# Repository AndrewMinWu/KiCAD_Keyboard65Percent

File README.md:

# Custom 65% Keyboard PCB

## Repository Structure

```text
├── Hardware/          # Schematic, PCB, and gerber files
├── Firmware/          # Firmware files
└── Libraries_And_Datasheets/              # Datasheets and libraries (from ai03) for keyboard parts. 
```

## Purpose & Motivation

When I was 15, I bought my first custom mechanical keyboard: a QK60 from Qwertykeys alongside Gateron yellow switches and some cheap keycaps from amazon. However, I encountered a problem when I accidently took out the PCB with the JST connector still plugged in, ripping the socket on the daughterboard (where the usb-c was). Devastated, this experience essentially brought me into PCB design through online guides and communities. 2 years later, with more PCB design experience, I decided to create my own 65% keyboard (my personal favorite form factor. Who uses the numpad anyways!?).     

## Design

### Component List (BOM)
1. ATmega32U4 8-bit AVR Microcontroller ([Datasheet](http://ww1.microchip.com/downloads/en/DeviceDoc/Atmel-7766-8-bit-AVR-ATmega16U4-32U4_Datasheet.pdf))
2. ECS-160 16.000MHz SMD Crystal 3225 4-Pin ([Datasheet](https://ecsxtal.com/store/pdf/ECX-32.pdf))
3. GCT USB4105-GF-A USB-C Receptacle 16P SMD RA ([Datasheet](https://gct.co/files/drawings/usb4105.pdf))
4. Keyboard Switches (MX, taken from ai03's library)
5. 1N4148 / 1N4148W Switching Diodes
6. Passives & Miscellaneous Hardware:
   - Capacitors (0805, Ceramic)
   - Resistors (0805)
   - Tactile Push Button (Reset Switch)

### PCB, Schematic, 3D Render

The full PCB was designed with KiCAD

## Firmware

The firmware for this keyboard is built using QMK. While the framework is C-based, configuring the board primarily involved utilizing the standard QMK file structure to define the hardware and layout:
* **`info.json` & `config.h`:** Keyboard matrix, MCU definitions, and hardware config
* **`rules.mk`:** Bootloader selection
* **`keymap.c`:** Keymap and layer definitions (able to change config with VIA)

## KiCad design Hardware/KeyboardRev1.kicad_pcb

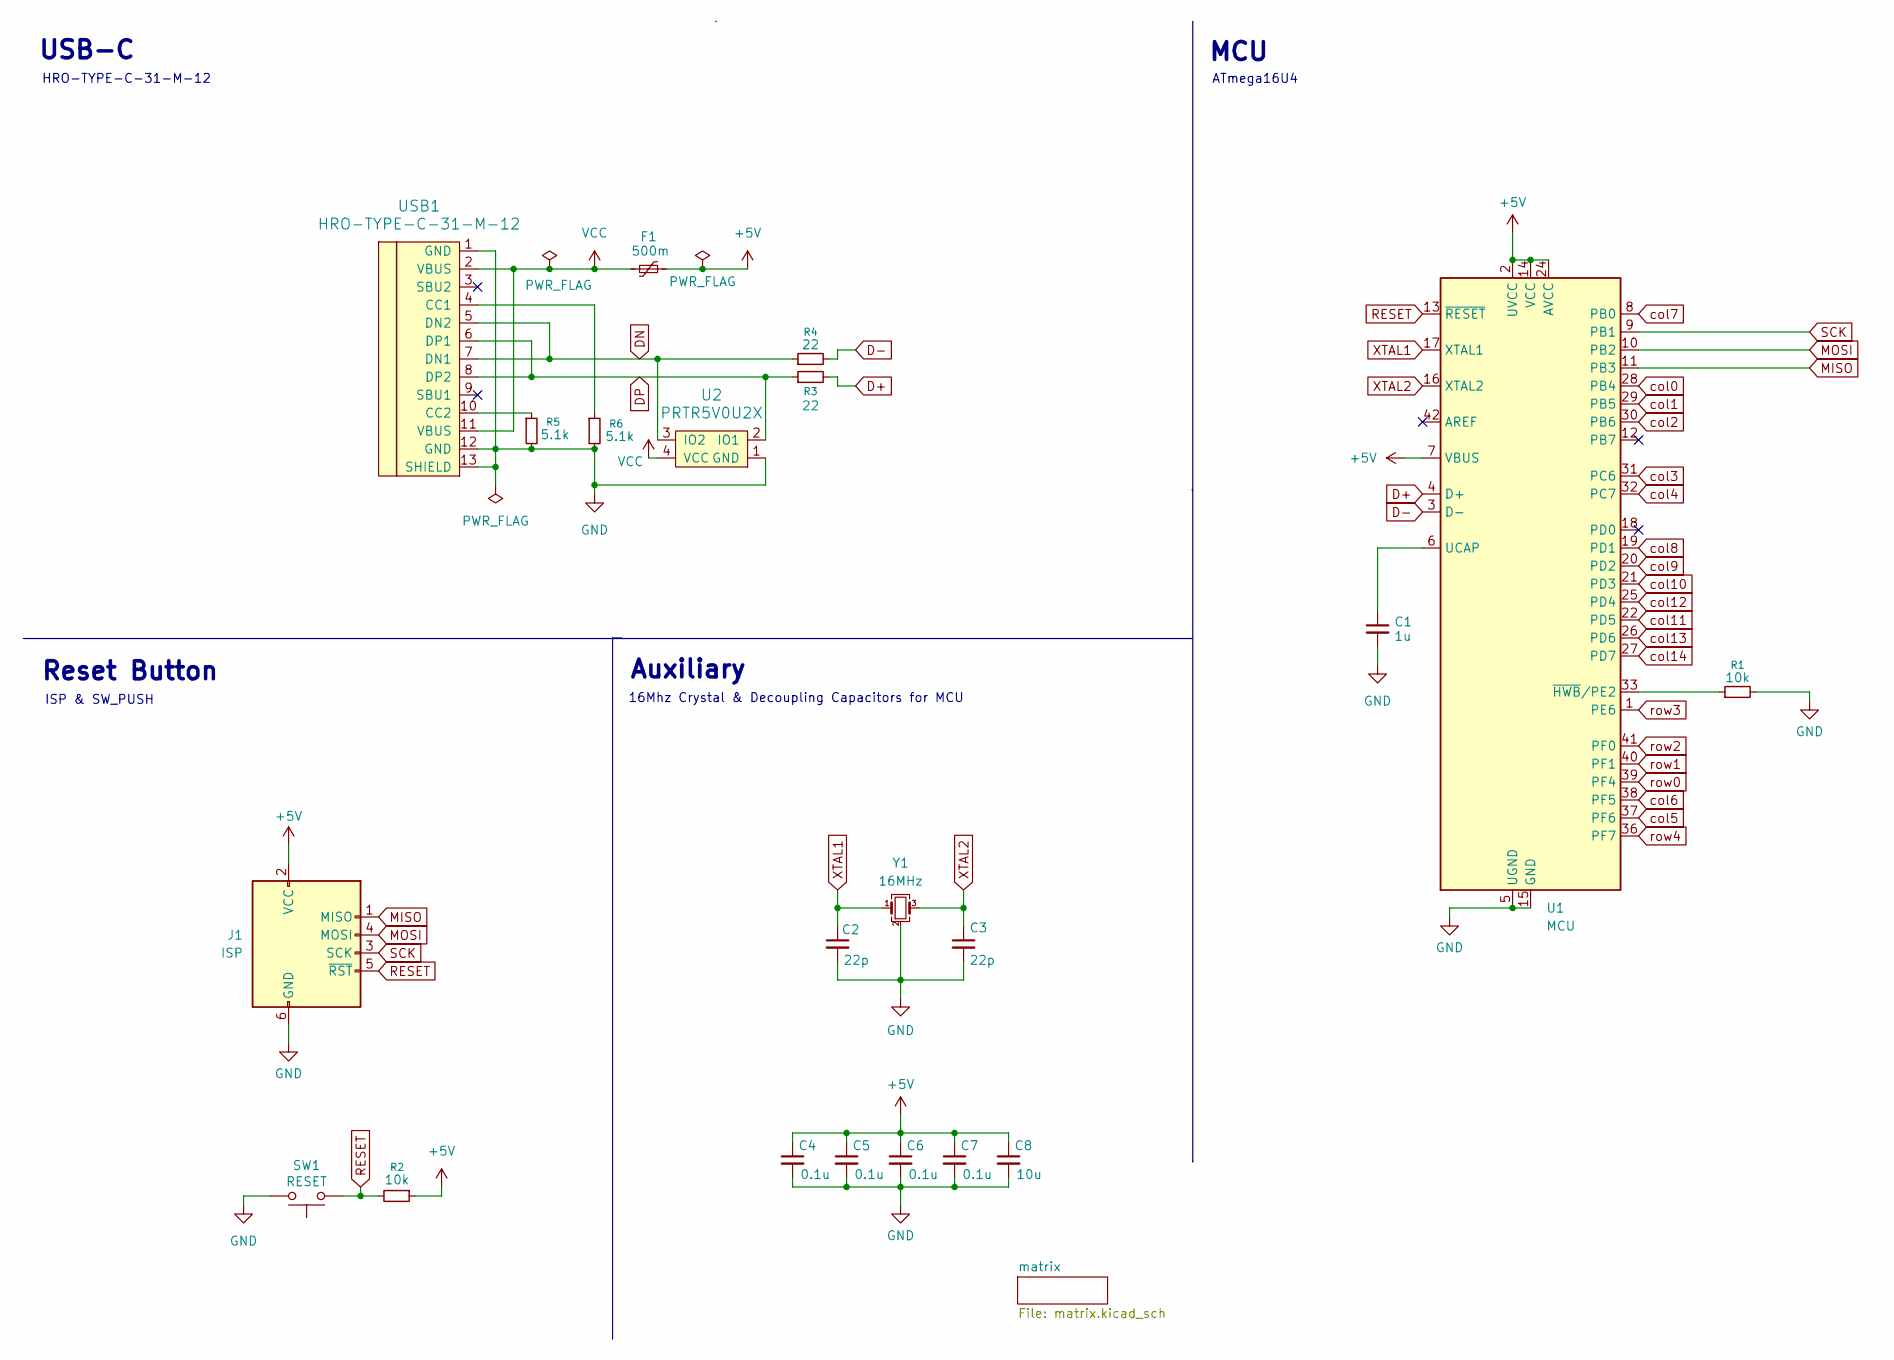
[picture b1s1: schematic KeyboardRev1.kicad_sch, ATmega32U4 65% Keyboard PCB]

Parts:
C1: 1u; C_0805_2012Metric_Pad1.18x1.45mm_HandSolder
C2, C3: 22p; C_0805_2012Metric_Pad1.18x1.45mm_HandSolder
C4, C5, C6, C7: 0.1u; C_0805_2012Metric_Pad1.18x1.45mm_HandSolder
C8: 10u; C_0805_2012Metric_Pad1.18x1.45mm_HandSolder
F1: 500m; Fuse_1206_3216Metric_Pad1.42x1.75mm_HandSolder
J1: ISP; Reset_Pretty-Mask
R1, R2: 10k; R_0805_2012Metric_Pad1.20x1.40mm_HandSolder
R3, R4: 22; R_0805_2012Metric_Pad1.20x1.40mm_HandSolder
R5, R6: 5.1k; R_0805_2012Metric_Pad1.20x1.40mm_HandSolder
SW1: RESET; SW_SPST_SKQG_WithStem
U1: MCU; TQFP-44_10x10mm_P0.8mm
U2: PRTR5V0U2X; SOT143B
USB1: HRO-TYPE-C-31-M-12; HRO-TYPE-C-31-M-12-HandSoldering
Y1: 16MHz; Crystal_SMD_3225-4Pin_3.2x2.5mm_HandSoldering

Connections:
+5V: C4.1, C5.1, C6.1, C7.1, C8.1, F1.2, J1.2 (VCC), R2.1, U1.2 (UVCC), U1.7 (VBUS), U1.14 (VCC), U1.24 (AVCC), U1.34 (VCC), U1.44 (AVCC)
D+: R3.2, U1.4 (D+)
D-: R4.2, U1.3 (D-)
DN: R4.1, U2.3 (IO2), USB1.5 (DN2), USB1.7 (DN1)
DP: R3.1, U2.2 (IO1), USB1.6 (DP1), USB1.8 (DP2)
GND: C1.2, C2.2, C3.2, C4.2, C5.2, C6.2, C7.2, C8.2, J1.6 (GND), R1.2, R5.2, R6.2, SW1.2, U1.5 (UGND), U1.15 (GND), U1.23 (GND), U1.35 (GND), U1.43 (GND), U2.1 (GND), USB1.1 (GND), USB1.12 (GND), USB1.13 (SHIELD), Y1.2 (G), Y1.4 (G)
MISO: J1.1 (MISO), U1.11 (PB3)
MOSI: J1.4 (MOSI), U1.10 (PB2)
unnamed: C1.1, U1.6 (UCAP)
unnamed: R1.1, U1.33 (~HWB/PE2)
unnamed: R6.1, USB1.4 (CC1)
unnamed: R5.1, USB1.10 (CC2)
RESET: J1.5 (~RST), R2.2, SW1.1, U1.13 (~RESET)
SCK: J1.3 (SCK), U1.9 (PB1)
VCC: F1.1, U2.4 (VCC), USB1.2 (VBUS), USB1.11 (VBUS)
XTAL1: C2.1, U1.17 (XTAL1), Y1.1
XTAL2: C3.1, U1.16 (XTAL2), Y1.3
col0: U1.28 (PB4); also elsewhere on the board
col1: U1.29 (PB5); also elsewhere on the board
col2: U1.30 (PB6); also elsewhere on the board
col3: U1.31 (PC6); also elsewhere on the board
col4: U1.32 (PC7); also elsewhere on the board
col5: U1.37 (PF6); also elsewhere on the board
col6: U1.38 (PF5); also elsewhere on the board
col7: U1.8 (PB0); also elsewhere on the board
col8: U1.19 (PD1); also elsewhere on the board
col9: U1.20 (PD2); also elsewhere on the board
col10: U1.21 (PD3); also elsewhere on the board
col11: U1.22 (PD5); also elsewhere on the board
col12: U1.25 (PD4); also elsewhere on the board
col13: U1.26 (PD6); also elsewhere on the board
col14: U1.27 (PD7); also elsewhere on the board
row0: U1.39 (PF4); also elsewhere on the board
row1: U1.40 (PF1); also elsewhere on the board
row2: U1.41 (PF0); also elsewhere on the board
row3: U1.1 (PE6); also elsewhere on the board
row4: U1.36 (PF7); also elsewhere on the board

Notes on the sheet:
16Mhz Crystal & Decoupling Capacitors for MCU
ATmega16U4
ISP & SW_PUSH
HRO-TYPE-C-31-M-12
Reset Button
USB-C
MCU
Auxiliary

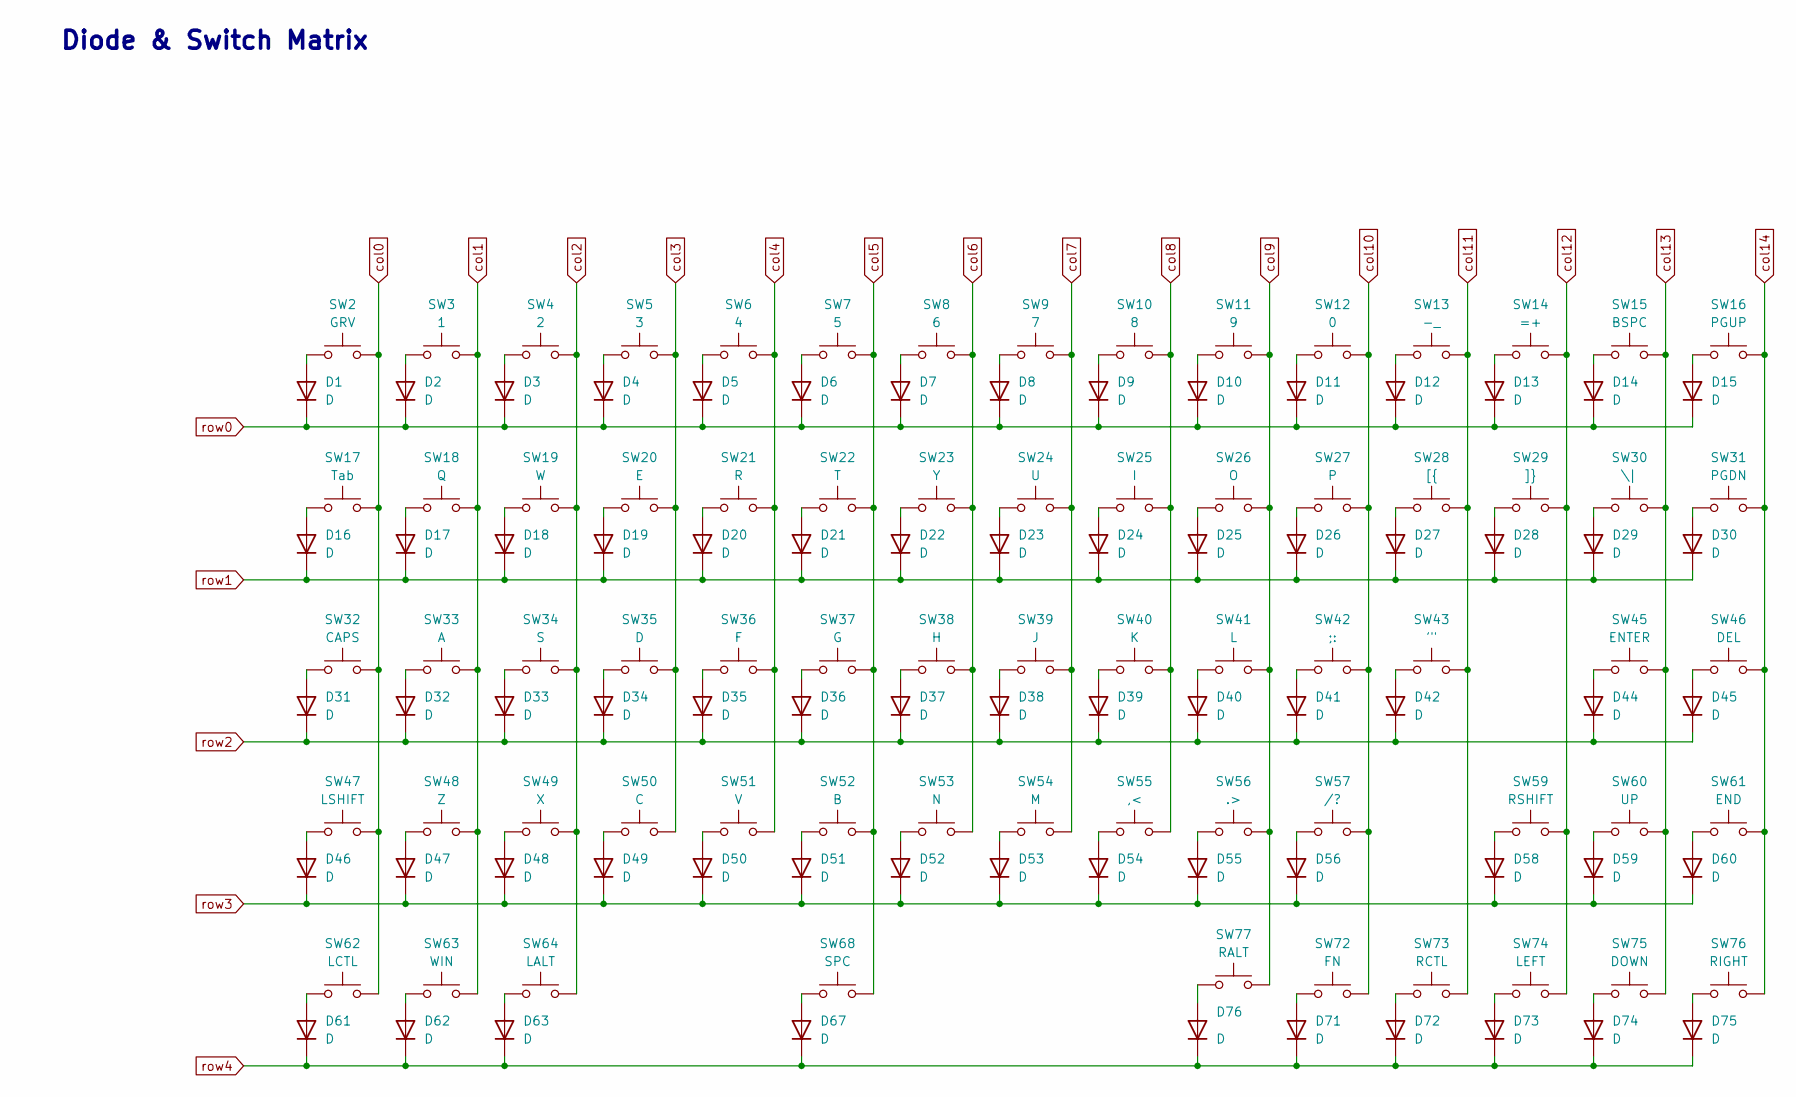
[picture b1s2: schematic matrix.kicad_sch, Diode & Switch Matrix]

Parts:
D1, D2, D3, D4, D5, D6, D7, D8, D9, D10, D11, D12, D13, D14, D15, D16, D17, D18, D19, D20, D21, D22, D23, D24, D25, D26, D27, D28, D29, D30, D31, D32, D33, D34, D35, D36, D37, D38, D39, D40, D41, D42, D44, D45, D46, D47, D48, D49, D50, D51, D52, D53, D54, D55, D56, D58, D59, D60, D61, D62, D63, D67, D71, D72, D73, D74, D75, D76: D; D_SOD-123
SW2: GRV; SW_Cherry_MX_1.00u_PCB
SW3: 1; SW_Cherry_MX_1.00u_PCB
SW4: 2; SW_Cherry_MX_1.00u_PCB
SW5: 3; SW_Cherry_MX_1.00u_PCB
SW6: 4; SW_Cherry_MX_1.00u_PCB
SW7: 5; SW_Cherry_MX_1.00u_PCB
SW8: 6; SW_Cherry_MX_1.00u_PCB
SW9: 7; SW_Cherry_MX_1.00u_PCB
SW10: 8; SW_Cherry_MX_1.00u_PCB
SW11: 9; SW_Cherry_MX_1.00u_PCB
SW12: 0; SW_Cherry_MX_1.00u_PCB
SW13: -_; SW_Cherry_MX_1.00u_PCB
SW14: =+; SW_Cherry_MX_1.00u_PCB
SW15: BSPC; SW_Cherry_MX_2.00u_PCB
SW16: PGUP; SW_Cherry_MX_1.00u_PCB
SW17: Tab; SW_Cherry_MX_1.50u_PCB
SW18: Q; SW_Cherry_MX_1.00u_PCB
SW19: W; SW_Cherry_MX_1.00u_PCB
SW20: E; SW_Cherry_MX_1.00u_PCB
SW21: R; SW_Cherry_MX_1.00u_PCB
SW22: T; SW_Cherry_MX_1.00u_PCB
SW23: Y; SW_Cherry_MX_1.00u_PCB
SW24: U; SW_Cherry_MX_1.00u_PCB
SW25: I; SW_Cherry_MX_1.00u_PCB
SW26: O; SW_Cherry_MX_1.00u_PCB
SW27: P; SW_Cherry_MX_1.00u_PCB
SW28: [{; SW_Cherry_MX_1.00u_PCB
SW29: ]}; SW_Cherry_MX_1.00u_PCB
SW30: \|; SW_Cherry_MX_1.50u_PCB
SW31: PGDN; SW_Cherry_MX_1.00u_PCB
SW32: CAPS; SW_Cherry_MX_1.75u_PCB
SW33: A; SW_Cherry_MX_1.00u_PCB
SW34: S; SW_Cherry_MX_1.00u_PCB
SW35: D; SW_Cherry_MX_1.00u_PCB
SW36: F; SW_Cherry_MX_1.00u_PCB
SW37: G; SW_Cherry_MX_1.00u_PCB
SW38: H; SW_Cherry_MX_1.00u_PCB
SW39: J; SW_Cherry_MX_1.00u_PCB
SW40: K; SW_Cherry_MX_1.00u_PCB
SW41: L; SW_Cherry_MX_1.00u_PCB
SW42: ;:; SW_Cherry_MX_1.00u_PCB
SW43: '"; SW_Cherry_MX_1.00u_PCB
SW45: ENTER; SW_Cherry_MX_2.25u_PCB
SW46: DEL; SW_Cherry_MX_1.00u_PCB
SW47: LSHIFT; SW_Cherry_MX_2.25u_PCB
SW48: Z; SW_Cherry_MX_1.00u_PCB
SW49: X; SW_Cherry_MX_1.00u_PCB
SW50: C; SW_Cherry_MX_1.00u_PCB
SW51: V; SW_Cherry_MX_1.00u_PCB
SW52: B; SW_Cherry_MX_1.00u_PCB
SW53: N; SW_Cherry_MX_1.00u_PCB
SW54: M; SW_Cherry_MX_1.00u_PCB
SW55: ,<; SW_Cherry_MX_1.00u_PCB
SW56: .>; SW_Cherry_MX_1.00u_PCB
SW57: /?; SW_Cherry_MX_1.00u_PCB
SW59: RSHIFT; SW_Cherry_MX_1.75u_PCB
SW60: UP; SW_Cherry_MX_1.00u_PCB
SW61: END; SW_Cherry_MX_1.00u_PCB
SW62: LCTL; SW_Cherry_MX_1.25u_PCB
SW63: WIN; SW_Cherry_MX_1.25u_PCB
SW64: LALT; SW_Cherry_MX_1.25u_PCB
SW68: SPC; SW_Cherry_MX_6.25u_PCB
SW72: FN; SW_Cherry_MX_1.00u_PCB
SW73: RCTL; SW_Cherry_MX_1.00u_PCB
SW74: LEFT; SW_Cherry_MX_1.00u_PCB
SW75: DOWN; SW_Cherry_MX_1.00u_PCB
SW76: RIGHT; SW_Cherry_MX_1.00u_PCB
SW77: RALT; SW_Cherry_MX_1.00u_PCB

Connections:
unnamed: D1.2 (A), SW2.1
unnamed: D2.2 (A), SW3.1
unnamed: D3.2 (A), SW4.1
unnamed: D4.2 (A), SW5.1
unnamed: D5.2 (A), SW6.1
unnamed: D6.2 (A), SW7.1
unnamed: D7.2 (A), SW8.1
unnamed: D8.2 (A), SW9.1
unnamed: D9.2 (A), SW10.1
unnamed: D10.2 (A), SW11.1
unnamed: D11.2 (A), SW12.1
unnamed: D12.2 (A), SW13.1
unnamed: D13.2 (A), SW14.1
unnamed: D14.2 (A), SW15.1
unnamed: D15.2 (A), SW16.1
unnamed: D16.2 (A), SW17.1
unnamed: D17.2 (A), SW18.1
unnamed: D18.2 (A), SW19.1
unnamed: D19.2 (A), SW20.1
unnamed: D20.2 (A), SW21.1
unnamed: D21.2 (A), SW22.1
unnamed: D22.2 (A), SW23.1
unnamed: D23.2 (A), SW24.1
unnamed: D24.2 (A), SW25.1
unnamed: D25.2 (A), SW26.1
unnamed: D26.2 (A), SW27.1
unnamed: D27.2 (A), SW28.1
unnamed: D28.2 (A), SW29.1
unnamed: D29.2 (A), SW30.1
unnamed: D30.2 (A), SW31.1
unnamed: D31.2 (A), SW32.1
unnamed: D32.2 (A), SW33.1
unnamed: D33.2 (A), SW34.1
unnamed: D34.2 (A), SW35.1
unnamed: D35.2 (A), SW36.1
unnamed: D36.2 (A), SW37.1
unnamed: D37.2 (A), SW38.1
unnamed: D38.2 (A), SW39.1
unnamed: D39.2 (A), SW40.1
unnamed: D40.2 (A), SW41.1
unnamed: D41.2 (A), SW42.1
unnamed: D42.2 (A), SW43.1
unnamed: D44.2 (A), SW45.1
unnamed: D45.2 (A), SW46.1
unnamed: D46.2 (A), SW47.1
unnamed: D47.2 (A), SW48.1
unnamed: D48.2 (A), SW49.1
unnamed: D49.2 (A), SW50.1
unnamed: D50.2 (A), SW51.1
unnamed: D51.2 (A), SW52.1
unnamed: D52.2 (A), SW53.1
unnamed: D53.2 (A), SW54.1
unnamed: D54.2 (A), SW55.1
unnamed: D55.2 (A), SW56.1
unnamed: D56.2 (A), SW57.1
unnamed: D58.2 (A), SW59.1
unnamed: D59.2 (A), SW60.1
unnamed: D60.2 (A), SW61.1
unnamed: D61.2 (A), SW62.1
unnamed: D62.2 (A), SW63.1
unnamed: D63.2 (A), SW64.1
unnamed: D67.2 (A), SW68.1
unnamed: D71.2 (A), SW72.1
unnamed: D72.2 (A), SW73.1
unnamed: D73.2 (A), SW74.1
unnamed: D74.2 (A), SW75.1
unnamed: D75.2 (A), SW76.1
unnamed: D76.2 (A), SW77.1
col0: SW2.2, SW17.2, SW32.2, SW47.2, SW62.2; also elsewhere on the board
col1: SW3.2, SW18.2, SW33.2, SW48.2, SW63.2; also elsewhere on the board
col2: SW4.2, SW19.2, SW34.2, SW49.2, SW64.2; also elsewhere on the board
col3: SW5.2, SW20.2, SW35.2, SW50.2; also elsewhere on the board
col4: SW6.2, SW21.2, SW36.2, SW51.2; also elsewhere on the board
col5: SW7.2, SW22.2, SW37.2, SW52.2, SW68.2; also elsewhere on the board
col6: SW8.2, SW23.2, SW38.2, SW53.2; also elsewhere on the board
col7: SW9.2, SW24.2, SW39.2, SW54.2; also elsewhere on the board
col8: SW10.2, SW25.2, SW40.2, SW55.2; also elsewhere on the board
col9: SW11.2, SW26.2, SW41.2, SW56.2, SW77.2; also elsewhere on the board
col10: SW12.2, SW27.2, SW42.2, SW57.2, SW72.2; also elsewhere on the board
col11: SW13.2, SW28.2, SW43.2, SW73.2; also elsewhere on the board
col12: SW14.2, SW29.2, SW59.2, SW74.2; also elsewhere on the board
col13: SW15.2, SW30.2, SW45.2, SW60.2, SW75.2; also elsewhere on the board
col14: SW16.2, SW31.2, SW46.2, SW61.2, SW76.2; also elsewhere on the board
row0: D1.1 (K), D2.1 (K), D3.1 (K), D4.1 (K), D5.1 (K), D6.1 (K), D7.1 (K), D8.1 (K), D9.1 (K), D10.1 (K), D11.1 (K), D12.1 (K), D13.1 (K), D14.1 (K), D15.1 (K); also elsewhere on the board
row1: D16.1 (K), D17.1 (K), D18.1 (K), D19.1 (K), D20.1 (K), D21.1 (K), D22.1 (K), D23.1 (K), D24.1 (K), D25.1 (K), D26.1 (K), D27.1 (K), D28.1 (K), D29.1 (K), D30.1 (K); also elsewhere on the board
row2: D31.1 (K), D32.1 (K), D33.1 (K), D34.1 (K), D35.1 (K), D36.1 (K), D37.1 (K), D38.1 (K), D39.1 (K), D40.1 (K), D41.1 (K), D42.1 (K), D44.1 (K), D45.1 (K); also elsewhere on the board
row3: D46.1 (K), D47.1 (K), D48.1 (K), D49.1 (K), D50.1 (K), D51.1 (K), D52.1 (K), D53.1 (K), D54.1 (K), D55.1 (K), D56.1 (K), D58.1 (K), D59.1 (K), D60.1 (K); also elsewhere on the board
row4: D61.1 (K), D62.1 (K), D63.1 (K), D67.1 (K), D71.1 (K), D72.1 (K), D73.1 (K), D74.1 (K), D75.1 (K), D76.1 (K); also elsewhere on the board

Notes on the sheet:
Diode & Switch Matrix

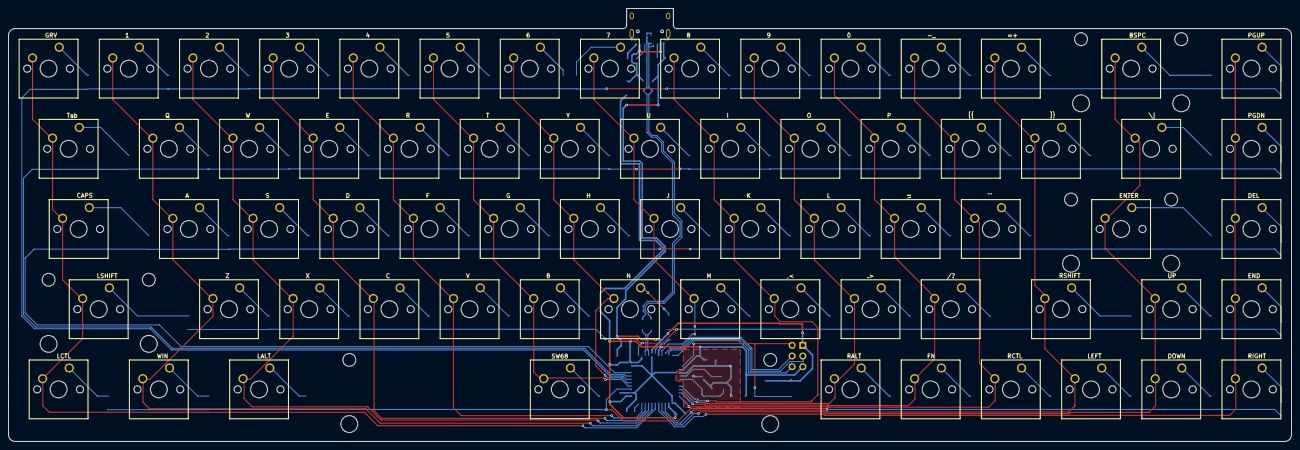
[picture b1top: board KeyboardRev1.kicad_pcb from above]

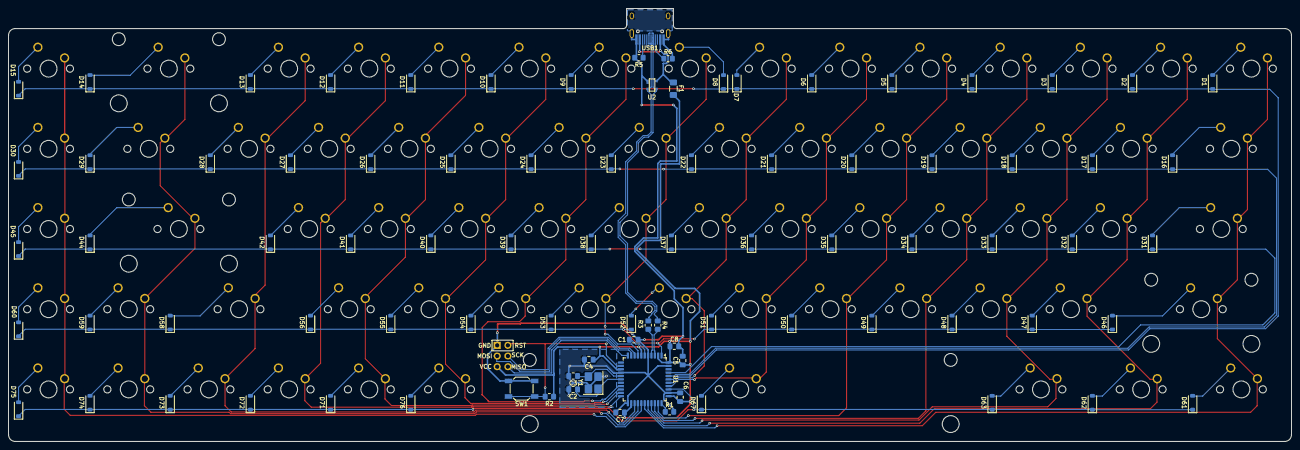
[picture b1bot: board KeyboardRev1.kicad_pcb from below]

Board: 2 copper layers, 304.8 x 102.9 mm, 157 parts (89 on the bottom side), 105 nets.
